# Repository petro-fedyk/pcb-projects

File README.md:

# pcb-project
Welcome!
Here I share my PCB design projects created in KiCad and Altium Designer.
Each board was made for learning, experimentation, or practical applications.

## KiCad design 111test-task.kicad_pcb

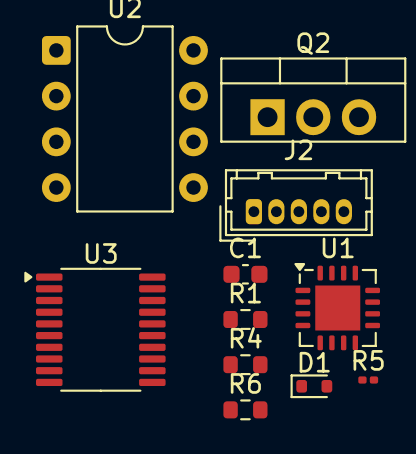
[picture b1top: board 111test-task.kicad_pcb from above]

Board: 2 copper layers, 11 parts (0 on the bottom side), 12 nets, no tracks yet.

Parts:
C1: C; C_0603_1608Metric
D1: 1N4148WT; D_SOD-523
J2: Conn_01x05_Pin; Hirose_DF13-05P-1.25DSA_1x05_P1.25mm_Vertical
Q2: IRLZ44N; TO-220-3_Vertical
R1, R6: 10k; R_0603_1608Metric
R4: 1k; R_0603_1608Metric
R5: 100; R_0201_0603Metric
U1: MCP2221AxML; QFN-16-1EP_4x4mm_P0.65mm_EP2.5x2.5mm
U2: OPA551P; DIP-8_W7.62mm
U3: INA253; TSSOP-20_4.4x6.5mm_P0.65mm

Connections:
ADC: U1.1 (GP0), U3.13 (OUT)
DAC: C1.1, R5.1, U1.2 (GP1), U2.3 (+)
FEEDBACK: J2.1, R5.2, U1.6 (GP2), U2.6
GND: C1.2, J2.3, U1.13 (VSS), U2.2 (-), U2.4 (V-), U3.6 (GND), U3.10 (REF2), U3.11 (REF1), U3.15 (GND)
MOSFET: R4.1, U1.7 (GP3)
unnamed: J2.4, U1.9 (SCL)
unnamed: J2.5, R1.2, U1.8 (SDA)
unnamed: Q2.1 (G), R4.2
unnamed: R6.2, U3.9 (VS)
OUT_SH: J2.2, U3.1 (IS-), U3.2 (IS-), U3.3 (IS-), U3.5 (IN-)
SENSING: Q2.3 (S), U3.16 (IN+), U3.18 (IS+), U3.19 (IS+), U3.20 (IS+)
VCC: D1.1 (K), Q2.2 (D), R1.1, R6.1, U1.16 (VDD), U2.7 (V+)

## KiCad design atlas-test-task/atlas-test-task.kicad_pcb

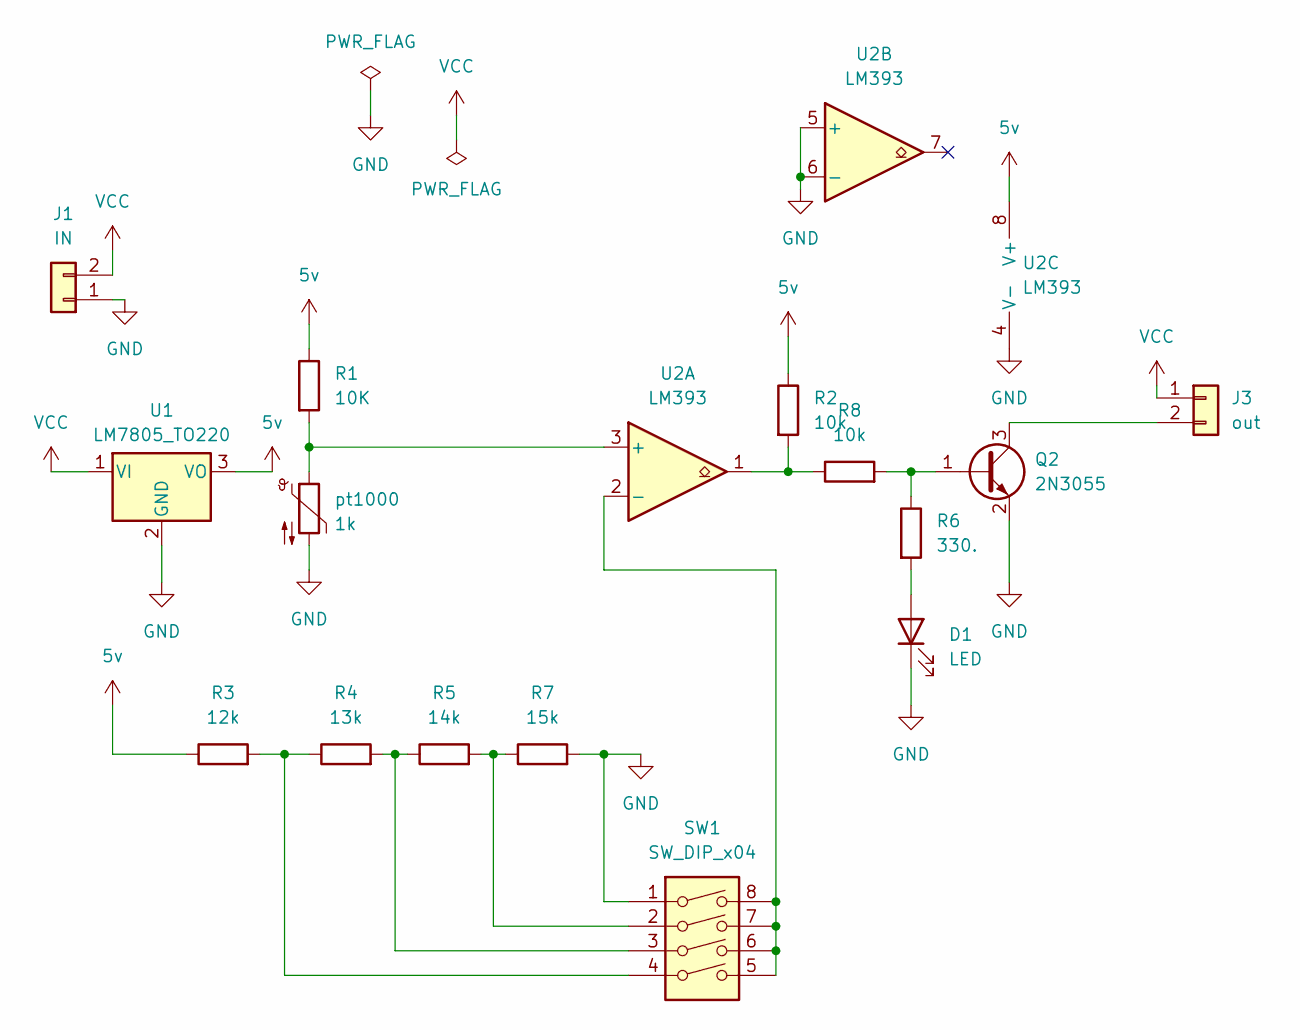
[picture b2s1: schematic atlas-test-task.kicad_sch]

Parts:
D1: LED; LED_D3.0mm
J1: IN; JWT_A3963_1x02_P3.96mm_Vertical
J3: out; JWT_A3963_1x02_P3.96mm_Vertical
Q2: 2N3055; TO-3P-3_Horizontal_TabDown
R1: 10K; R_Axial_DIN0204_L3.6mm_D1.6mm_P2.54mm_Vertical
R2, R8: 10k; R_Axial_DIN0204_L3.6mm_D1.6mm_P2.54mm_Vertical
R3: 12k; R_Axial_DIN0204_L3.6mm_D1.6mm_P2.54mm_Vertical
R4: 13k; R_Axial_DIN0204_L3.6mm_D1.6mm_P2.54mm_Vertical
R5: 14k; R_Axial_DIN0204_L3.6mm_D1.6mm_P2.54mm_Vertical
R6: 330.; R_Axial_DIN0204_L3.6mm_D1.6mm_P2.54mm_Vertical
R7: 15k; R_Axial_DIN0204_L3.6mm_D1.6mm_P2.54mm_Vertical
SW1: SW_DIP_x04; SW_DIP_SPSTx04_Slide_6.7x11.72mm_W7.62mm_P2.54mm_LowProfile
U1: LM7805_TO220; TO-220-3_Vertical
U2: LM393; DIP-8_W7.62mm
pt1000: 1k; R_Axial_DIN0204_L3.6mm_D1.6mm_P2.54mm_Vertical

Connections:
5v: R1.1, R2.1, R3.1, U1.3 (VO), U2.8 (V+)
GND: D1.1 (K), J1.1, Q2.2 (E), R7.2, SW1.1, U1.2 (GND), U2.4 (V-), U2.5 (+), U2.6 (-), pt1000.2
unnamed: D1.2 (A), R6.2
unnamed: J3.2, Q2.3 (C)
unnamed: Q2.1 (B), R6.1, R8.2
unnamed: R2.2, R8.1, U2.1
unnamed: R3.2, R4.1, SW1.4
unnamed: R4.2, R5.1, SW1.3
unnamed: R5.2, R7.1, SW1.2
unnamed: R1.2, U2.3 (+), pt1000.1
unnamed: SW1.5, SW1.6, SW1.7, SW1.8, U2.2 (-)
VCC: J1.2, J3.1, U1.1 (VI)

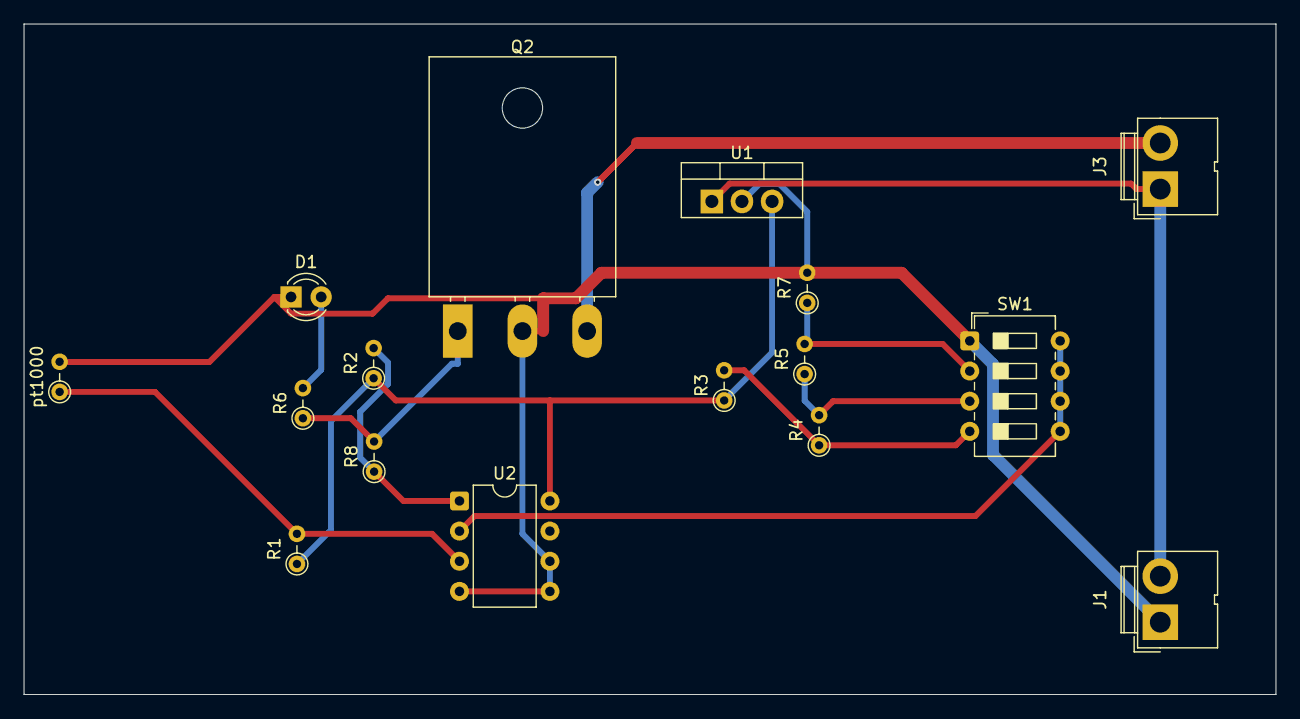
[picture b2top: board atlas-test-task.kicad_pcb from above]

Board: 2 copper layers, 105.5 x 56.5 mm, 16 parts (0 on the bottom side), 12 nets.

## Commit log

2025-10-25 Enhance README with project details and welcome message
    Added a welcome message and project description.
